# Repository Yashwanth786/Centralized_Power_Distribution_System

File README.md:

<div align="center">

# Centralized Power Distribution System

### IIT Hyderabad — Electrical Engineering Laboratory

*An IoT-based smart power management system for EE lab workbenches. Students request table power through a web portal by entering their roll number; lab staff monitor and control all 10 tables in real time from a central dashboard — powered by ESP32-C3 microcontrollers, Firebase Realtime Database, and automatic 18650 Li-Ion battery backup.*

<br>

<br>

</div>

---

## Table of Contents

1. [Introduction & Overview](#1-introduction--overview)
2. [Features](#2-features)
3. [System Architecture](#3-system-architecture)
4. [How It Works](#4-how-it-works)
5. [Hardware Design](#5-hardware-design)
6. [Software Design & Frameworks](#6-software-design--frameworks)
7. [Repository Structure](#7-repository-structure)
8. [Setup & Workflow](#8-setup--workflow)
9. [How to Run](#9-how-to-run)
10. [Portal Walkthrough — Screenshots](#10-portal-walkthrough--screenshots)
11. [Demo Video](#11-demo-video)
12. [Applications](#12-applications)
13. [Challenges Faced](#13-challenges-faced)
14. [Future Improvements](#14-future-improvements)
15. [Team](#15-team)

---

## 1. Introduction & Overview

University EE labs share 10 workbenches between many student groups. Today, a lab staff member must physically walk to each table to switch power on or off, and there is no record of who used which table, when, or for how long. Power is sometimes left ON after students leave, equipment runs unattended, and there is no centralized emergency cut-off.

The **Centralized Power Distribution System (CPDS)** eliminates this entirely. A custom PCB at each table drives three relay-controlled socket outlets under the control of a cloud-connected **Seeed Studio XIAO ESP32-C3**. A **React + Firebase** web portal provides two portals in one URL — a **Student Portal** where students type their roll number and choose an available table, and a **Staff Dashboard** where one instructor sees all 10 tables live and can cut any session in one click.

Communication flows through **Firebase Realtime Database** — the portal writes `isOn: true` to a table's path, the ESP32 there reads it within 2 seconds and closes the relays, and the sockets go live. All events are logged with timestamps. A built-in 18650 Li-Ion battery automatically takes over if mains power is lost, and a physical emergency button on each table cuts power instantly without needing a network round-trip.

---

## 2. Features

| Feature | Description |
|---|---|
| **Manual Roll Number Entry** | Students type their roll number in the portal — no QR scan, no app install, works on any browser |
| **Live Table Availability** | Student portal dropdown shows only currently available (unoccupied) tables in real time |
| **3-Hour Session Timer** | Each table allocation runs for 3 hours; staff dashboard shows live countdown per table |
| **Staff Dashboard** | Live grid of all 10 tables: status badge, student roll, session start time, countdown, power source, and action button |
| **Firebase Real-Time Sync** | Portal ↔ ESP32 changes propagate in under 2 seconds via Firebase `onValue` listeners |
| **Mains / Battery Auto-Failover** | ADC on GPIO D0 monitors mains via voltage divider; AO3401A P-MOSFET switches to 18650 + MT3608 boost when mains drops |
| **Physical Emergency Button** | NO push button on each table — immediately cuts all 3 relays and writes to Firebase without waiting for a network response |
| **Bi-Color LED Indicator** | Green = mains present & running; Red = battery mode / error / boot |
| **10-Second Heartbeat** | Each ESP32 writes `lastSeen` every 10 s; dashboard shows 🔴 Offline if heartbeat stops |
| **Activity Log Panel** | Every session start, end, expiry, emergency, and power event is logged to Firebase with a human-readable timestamp |
| **All-Off Emergency Button** | Staff button with confirmation modal cuts power to all 10 tables simultaneously |
| **Session Auto-Expiry** | Dashboard `Countdown` component auto-calls `deallocateTable()` when a 3-hour session reaches zero |
| **Recent Allocations Table** | Student roll-entry page shows the last 5 active allocations live — helps students see if their table is already taken |

---

## 3. System Architecture

```
┌──────────────────────────────────────────────────────────────────────┐
│                          Firebase Cloud                              │
│                                                                      │
│   Realtime Database                    Firebase Hosting              │
│   ────────────────                     ────────────────              │
│   tables/T-XX/isOn          ◄──────    React Web Portal             │
│   tables/T-XX/studentRoll              ├── Student Portal            │
│   tables/T-XX/starttimeLabel  ──────►  │   Roll number entry         │
│   tables/T-XX/sessionEnd               │   Table selection           │
│   power/T-XX/source         ◄──────    │   Confirmation screen       │
│   power/T-XX/lastSeen                  └── Staff Dashboard           │
│   logs/{id}                                All 10 tables live        │
│   logCount                                 End Session / All Off     │
└──────────────────────┬───────────────────────────────────────────────┘
                       │  Wi-Fi  IEEE 802.11 b/g/n
         ┌─────────────┼──────────────┐
         │             │              │
   ┌─────▼──────┐ ┌────▼───────┐ ┌──▼──────────┐
   │  Table T-01│ │ Table T-02 │ │  Table T-10  │
   │ XIAO ESP32 │ │ XIAO ESP32 │ │  XIAO ESP32  │
   │ Custom PCB │ │ Custom PCB │ │  Custom PCB  │
   │ ULN2003APG │ │ ULN2003APG │ │  ULN2003APG  │
   │ 3× Relays  │ │ 3× Relays  │ │  3× Relays   │
   │ HLK-PM01   │ │ HLK-PM01   │ │  HLK-PM01    │
   │ 18650+MT36 │ │ 18650+MT36 │ │  18650+MT36  │
   │ Emerg Btn  │ │ Emerg Btn  │ │  Emerg Btn   │
   │ Bi-clr LED │ │ Bi-clr LED │ │  Bi-clr LED  │
   └────────────┘ └────────────┘ └──────────────┘
```

**Data flow summary:**
- Student submits roll number → `allocateTable(id, roll)` → Firebase `tables/T-XX/isOn = true`
- ESP32 polls Firebase every 2 s → reads `isOn = true` → `setRelays(true)` → sockets live
- ESP32 writes `power/T-XX/lastSeen` every 10 s → dashboard flags Offline if missed
- Staff clicks End Session → `deallocateTable(id)` → Firebase `isOn = false` → ESP32 reads → relays open

---

## 4. How It Works

### Student Flow

```
Student opens web portal on any browser
              │
              ▼
Home Page  →  clicks "Student Portal" card
              │
              ▼
Roll Number Entry page (StudentScanPage):
  - Text input: type roll number e.g. "EE22BTECH11001"  →  press Next / Enter
  - Recent Allocations table shows last 5 active sessions live from Firebase
              │
              ▼
Table Selection page (StudentSelectPage):
  - Dropdown populated in real time with ONLY unoccupied tables
  - Occupied tables are excluded automatically
  - If all tables are full → yellow warning banner appears
  - Student selects table  →  "Allocate Table"
              │
              ▼
allocateTable("T-03", "EE22BTECH11001") writes to Firebase:
     tables/T-03/isOn            = true
     tables/T-03/studentRoll     = "EE22BTECH11001"
     tables/T-03/starttimeLabel  = "07/05/2026, 03:45:12 pm"
     tables/T-03/sessionEnd      = <epoch ms + 3 hours>
     tables/T-03/sessionEndLabel = "07/05/2026, 06:45:12 pm"
     logs/{n}                    = { type: "session_start", ... }
              │
              ▼
Confirmation page (StudentConfirmPage):
  - Shows roll number + table number (large green)
  - "Power is ON — please go to the table"
  - Session duration: 3 Hours
  - Auto-redirects to home in 5 seconds
              │
              ▼
ESP32 at T-03: polls Firebase (every 2 s)
  reads isOn = true  →  setRelays(true)
  D4, D3, D2 HIGH  →  ULN2003 drives coils  →  relay contacts close  →  sockets LIVE
  Green LED ON
```

### Staff Flow

```
Staff opens portal  →  "Technical Staff Portal"  →  Password entry
              │
              ▼
StaffLoginPage:
  - Password compared against hardcoded STAFF_PASSWORD
  - Correct  →  sessionStorage.setItem("staffAuth","true")  →  navigate to dashboard
  - Wrong    →  inline error message, password cleared
              │
              ▼
StaffDashboardPage (auth guard: redirects if staffAuth not set):
  - Three Firebase listeners started on mount:
      subscribeToTables  →  setTables state
      subscribeToPower   →  setPower  state
      subscribeToLogs    →  setLogs   state
  - Cleanup: all three unsubscribed on unmount
              │
              ▼
Dashboard header shows live stats chips: "3 Occupied  |  6 Available  |  1 Offline"

Dashboard table row per T-01…T-10:
  [Table ID] [Status badge] [Student Roll] [Start Time] [Countdown] [Power badge] [Action]
              │
              ▼
Staff clicks "⛔ End Session" on T-03:
  →  deallocateTable("T-03", "staff_ended")
  →  Firebase: isOn=false, lastUsed=<now>
  →  log: { type:"session_end", message:"Table T-03 session ended — reason: staff_ended" }
  →  ESP32 reads isOn=false on next 2s poll  →  setRelays(false)  →  sockets dead
              │
              ▼
Staff clicks "⛔ ALL OFF"  →  confirmation modal appears
  →  "Yes, ALL OFF"  →  allTablesOff()
  →  Promise.all: all 10 tables set isOn=false simultaneously
  →  log: { type:"staff", message:"ALL TABLES turned OFF by staff" }
```

### Emergency Button (Hardware)

```
Student presses NO push button on table edge (GPIO D1, INPUT_PULLUP)
              │
              ▼
ESP32 loop: digitalRead(PIN_EMERG_BTN) = LOW
50 ms debounce elapsed, btnWasPressed was false
              │
              ▼
emergTripped = true
setRelays(false) IMMEDIATELY — no Firebase wait
D4, D3, D2 → LOW  →  relay contacts open  →  sockets DEAD
              │
              ▼
Firebase writes (best-effort):
  firebaseDeallocate("emergency_button")  →  tables/T-XX/isOn = false
  firebaseAddLog("Emergency button pressed — relays OFF", "emergency")
Red LED ON
              │
              ▼
Button released: btnWasPressed=false, emergTripped=false (auto-reset latch)
Table ready for next student
```

### Mains Failure & Battery Failover

```
Mains power drops  →  HLK-PM01 output falls
              │
              ▼
ADC on GPIO D0 reads voltage divider:  analogRead(PIN_MAINS_ADC) < 500
mains (bool) becomes false, lastMailsState was true → change detected
              │
              ▼
updateLED(false): Green OFF, Red ON
firebaseSetPower("battery"):
  power/T-XX/source   = "battery"
  power/T-XX/lastSeen = <readable time>
              │
              ▼
If relays were ON when mains dropped:
  setRelays(false)
  firebaseDeallocate("mains_lost")
  firebaseAddLog("Mains power lost — relays turned OFF", "power")
              │
              ▼
AO3401A P-MOSFET hardware path (automatic, no firmware needed):
  HLK-PM01 rail drops  →  MOSFET gate control switches
  18650 Li-Ion  →  MT3608 boost converter  →  5V rail maintained
  ESP32 and relays stay powered
              │
              ▼
Mains restored: ADC rises above 500, mains=true again
updateLED(true): Green ON, Red OFF
firebaseSetPower("mains")
firebaseAddLog("Mains power restored", "power")
```

---

## 5. Hardware Design

### PCB Overview

Custom 2-layer PCB designed in **KiCad 9**. One board per lab table — 10 boards total.

| Parameter | Value |
|---|---|
| Design Tool | KiCad 9.x |
| Layers | 2 — F.Cu (signal + power) / B.Cu (High Voltage AC Power) |
| Min trace width | 0.3 mm signal / 1.5 mm mains |
| Mains isolation | 3 mm creepage gap + PCB slot (Edge.Cuts) |
| Surface finish | HASL |
| Board thickness | 1.6 mm |
| Copper weight | 1 oz (35 µm) |

### Schematic

### PCB Layout

### Pin Map — XIAO ESP32-C3

| Label | GPIO | Direction | Function |
|---|---|---|---|
| D0 | 2 | INPUT (ADC 12-bit) | Voltage divider output — mains sense, threshold 500 |
| D1 | 3 | INPUT (INPUT_PULLUP) | Emergency button — NO contact, active LOW |
| D2 | 4 | OUTPUT | ULN2003 I3 → Relay 3 — HIGH = relay energised = socket ON |
| D3 | 5 | OUTPUT | ULN2003 I2 → Relay 2 |
| D4 | 6 | OUTPUT | ULN2003 I1 → Relay 1 |
| D5 | 7 | OUTPUT | Green LED — HIGH = mains present, no error |
| D10 | 10 | OUTPUT | Red LED — HIGH = battery mode / error / boot |

### Power Architecture

```
230V AC Mains
     │
 [Varistor MOV]   ← surge protection
     │
 [HLK-PM01]       ← isolated SMPS, 230VAC → 5V DC
     │
     ├──────────── 5V Rail ─────────────────────────────────────┐
     │                                                          │
     │         [TP4056 charger] ←─── charges 18650 from 5V     │
     │                │                                         │
     │           [18650 Li-Ion]                                 │
     │                │                                         │
     │           [MT3608 Boost] → 5V                            │
     │                │                                      [AO3401A P-MOSFET]
     │                └─────────────────────────────────────────┘
     │                                                          │
     └──────────────────────────── 5V Supply Rail ─────────────┘
                                         │
                              [ESP32-C3 + ULN2003 + 3× Relays]
```

- **Normal:** HLK-PM01 supplies the 5V rail; AO3401A gate held high → MOSFET OFF → battery path blocked
- **Mains failure:** HLK-PM01 drops; AO3401A switches → MT3608 boosts 18650 → 5V rail sustained
- **Charging:** TP4056 charges 18650 from the 5V mains rail while mains is present
- **Protection:** SS34 Schottky diodes on all relay flyback paths; Varistor on AC input for surge events

### Bill of Materials (BOM)

| # | Component | Description | MPN | Price (Rs.) | Qty |
|---|---|---|---|---|---|
| 1 | Seeed Studio XIAO ESP32-C3 | Wi-Fi microcontroller, USB-C, castellated | Generic | 600 | 1 |
| 2 | 5V 1-Channel Relay Module | SRD-05VDC-SL-C coil, 10A contacts | SRD-05VDC-SL-C | 33 | 3 |
| 3 | ULN2003APG (Toshiba) | 50V / 500mA 7-ch Darlington array — relay driver | ULN2003APG | 19 | 1 |
| 4 | Momentary Push Switch | NO contact, active-low emergency button | TSD001B07018A | 20 | 1 |
| 5 | Hi-Link HLK-PM01 | 230VAC → 5V / 3W isolated SMPS | HLK-PM01 | 200 | 1 |
| 6 | 18650 Li-Ion Battery | 3.7V, 2500mAh backup cell | INR18650-25P | 81 | 1 |
| 7 | 18650 Battery Holder | SMD/SMT single cell | 1042P | 33 | 1 |
| 8 | TP4056 Charging Module | Adjustable 1A Li-Ion charger | TP4056 | 14 | 1 |
| 9 | MT3608 Boost Converter | 2A max DC-DC step-up module | MT3608| 36 | 1 |
| 10 | Bi-Color LED | 5mm Red/Green dual indicator | XL-A524SURSYGW | 3 | 1 |
| 11 | 6-Pin DPDT Self-Lock Switch | Latching power switch | — | 6 | 1 |
| 12 | AO3401A MOSFET | P-channel SOT-23, mains/battery path switch | AO3401A | 4 | 1 |
| 13 | 3-Pin Screw Terminal | 3.5mm pitch — mains & load connections | XY302V-3.5-3P | 12 | 4 |
| 14 | SS34 Schottky Diode | 3A / 40V — relay flyback + path blocking | — | 7 | 4 |
| 15 | 22µH Inductor SMD | MT3608 boost converter inductor | ASPI-0630LR-220M-T15 | 70 | 1 |
| 16 | Varistor D15.5mm P7.5mm | MOV surge protection on AC input | 561KD10J | 14 | 1 |
| 17 | PCB | Total PCB manufacturing cost  | — | 2936 | 1 |

Total cost  = Rs. 4211 /-  per  Table.

### Component Footprints

| Component | KiCad Footprint | Library |
|---|---|---|
| XIAO ESP32-C3 | `SeeedStudio_XIAO_ESP32C3` | Custom (castellated pads) |
| Relay Module | `Relay_THT:HF41F` | Standard |
| ULN2003APG | `Package_DIP:DIP-16_W7.62mm` | Standard |
| Momentary Push Switch | `Button_Switch_THT:SW_PUSH_6mm` | Standard |
| HLK-PM01 | `Converter_ACDC:HLK-PM01` | Standard |
| 18650 Battery Holder | `BatteryHolder_THT:BatteryHolder_Keystone_1042P` | Standard |
| TP4056 Module | `Module_TP4056` | Custom |
| MT3608 Boost Module | `Module_MT3608` | Custom |
| AO3401A MOSFET | `mosfet.pretty:SOT23-3` | Custom — included in `kicad/mosfet.pretty/` |
| Bi-Color LED | `LED_THT:LED_D5.0mm_2pin` | Standard |
| 3-Pin Screw Terminal | `TerminalBlock_Phoenix:MKDS_3-3.5` | Standard |
| 100µF Cap DIP | `Capacitor_THT:CP_Radial_D8.0mm_P3.50mm` | Standard |
| 22µF Cap DIP | `Capacitor_THT:CP_Radial_D6.3mm_P2.50mm` | Standard |
| SS34 Schottky Diode | `Diode_THT:D_DO-201AD` | Standard |
| 22µH Inductor SMD | `Inductor_SMD:L_Bourns_SRR1260` | Standard |
| All THT Resistors | `Resistor_THT:R_Axial_DIN0207_L6.3mm_D2.5mm_P7.62mm` | Standard |
| Varistor | `Varistor_THT:RV_D15.5mm_P7.5mm` | Standard |

> **Note:** The `mosfet.pretty/` folder is included in `kicad/` as a relative-path library. The project will open without missing footprint errors on any machine as long as the folder structure is kept intact.

---

## 6. Software Design & Frameworks

### Tech Stack

| Layer | Technology | Details |
|---|---|---|
| Frontend | React 18.2 | `create-react-app` scaffold |
| Routing | React Router DOM v6.21 | `BrowserRouter` + `Routes` + `Route` |
| Database | Firebase Realtime Database v10.7 | Real-time `onValue` listeners + `set` / `update` writes |
| Auth | Session-based (hardcoded password) | `sessionStorage.setItem("staffAuth","true")` |
| Hosting | Firebase Hosting | Deployed via `firebase deploy` |
| Firmware | Arduino / C++ on ESP32-C3 | `Firebase_ESP_Client` by Mobizt, `ArduinoJson` by Blanchon |

### Page Map

| Route | Component | What it does |
|---|---|---|
| `/` | `HomePage` | Landing — two hover cards: Technical Staff Portal & Student Portal |
| `/student/scan` | `StudentScanPage` | Roll number text input + Enter key support + recent allocations live table |
| `/student/select` | `StudentSelectPage` | Live dropdown of available tables + "Allocate Table" button + loading state |
| `/student/confirm` | `StudentConfirmPage` | Success card — roll, table (large green), "power is ON", 5-second countdown redirect |
| `/staff/login` | `StaffLoginPage` | Password input with show/hide toggle — stores auth in sessionStorage |
| `/staff/dashboard` | `StaffDashboardPage` | Full dashboard — 3 Firebase listeners, 10-table grid, logs panel, ALL OFF modal |

### Firebase Database Schema

```json
{
  "tables": {
    "T-01": {
      "isOn": true,
      "studentRoll": "EE22BTECH11001",
      "starttimeLabel": "07/05/2026, 03:45:12 pm",
      "sessionEnd": 1715079912000,
      "sessionEndLabel": "07/05/2026, 06:45:12 pm"
    }
  },
  "power": {
    "T-01": {
      "source": "mains",
      "lastSeen": "07/05/2026, 03:50:00 pm"
    }
  },
  "logs": {
    "1": {
      "message": "Table T-01 allocated to student EE22BTECH11001",
      "tableId": "T-01",
      "type": "session_start",
      "timestamp": "07/05/2026, 03:45:12 pm"
    }
  },
  "logCount": 1
}
```

### Key Functions — `database.js`

| Function | Description |
|---|---|
| `subscribeToTables(cb)` | `onValue` on `tables/` — returns Firebase unsubscribe fn; called in useEffect cleanup |
| `subscribeToPower(cb)` | `onValue` on `power/` — same pattern |
| `subscribeToLogs(cb, limit)` | `onValue` on `logs/` with `orderByKey + limitToLast(100)`, sorted newest-first |
| `allocateTable(id, roll)` | Writes `isOn=true`, roll, start time label, sessionEnd epoch + label; adds `session_start` log |
| `deallocateTable(id, reason)` | Writes `isOn=false`, `lastUsed`; adds `session_end` or `expire` log based on reason |
| `allTablesOff()` | `Promise.all` over all 10 table deallocations; adds single `staff` log |
| `clearLogs()` | Sets `logs` and `logCount` to null/0 |
| `clearAllData()` | Called on `App.js` mount — resets all tables to `isOn:false` and power to `offline` |
| `addLog({message, tableId, type})` | Reads `logCount`, increments, writes to `logs/{n}` with human timestamp |
| `toReadable(ms)` | Formats epoch ms → `"DD/MM/YYYY, HH:MM:SS am/pm"` (matches ESP32 output) |

### ESP32 Firmware — Timing Constants

| `#define` | Value | Purpose |
|---|---|---|
| `MAINS_THRESHOLD` | 500 (ADC counts) | 12-bit ADC reading below this = mains lost |
| `DEBOUNCE_MS` | 50 ms | Emergency button software debounce window |
| `FIREBASE_POLL_MS` | 2000 ms | Interval between Firebase `getBool` reads for `isOn` |
| `HEARTBEAT_INTERVAL_MS` | 10000 ms | Interval between `lastSeen` + power source writes |

### App.js — Startup Behaviour

On every portal load, `App.js` calls `clearAllData()` in a `useEffect`. This resets all 10 tables to `isOn: false` and all power entries to `source: "offline"` — ensuring a clean slate each time staff open the portal.

---

## 7. Repository Structure

```
centralized-power-distribution/
│
├── README.md                              ← This file
├── PCB.pdf                                ← Hardware reference (schematic, BOM, footprints, gerbers)
├── .gitattributes
│
├── kicad/                                 ← All KiCad design files
│   ├── lab.kicad_pro                      ← Open this in KiCad 7 to load the full project
│   ├── lab.kicad_sch                      ← Complete schematic
│   ├── lab.kicad_pcb                      ← PCB layout with copper pours and component placements
│   ├── lab.kicad_prl                      ← Project-level layer/render preferences
│   ├── New_Library.kicad_sym              ← Custom schematic symbols library
│   ├── mosfet.kicad_sym                   ← AO3401A schematic symbol
│   ├── mosfet.pretty/
│   │   └── SOT23-3.kicad_mod              ← Custom AO3401A PCB footprint (SOT-23-3, 0.95mm pitch)
│   ├── sym-lib-table                      ← Symbol library path references
│   ├── fp-lib-table                       ← Footprint library path references
│   └── lab_output/                        ← Gerber files — ZIP this folder and send to manufacturer
│       ├── lab-F_Cu.gbr                   ← Front copper traces
│       ├── lab-B_Cu.gbr                   ← Back copper ground plane
│       ├── lab-F_Mask.gbr                 ← Front solder mask
│       ├── lab-B_Mask.gbr                 ← Back solder mask
│       ├── lab-F_Silkscreen.gbr           ← Front silkscreen labels
│       ├── lab-B_Silkscreen.gbr           ← Back silkscreen
│       ├── lab-F_Paste.gbr                ← Front solder paste
│       ├── lab-B_Paste.gbr                ← Back solder paste
│       ├── lab-Edge_Cuts.gbr              ← Board outline + isolation PCB slot
│       ├── lab-PTH.drl                    ← Plated through-hole drill file
│       ├── lab-NPTH.drl                   ← Non-plated through-hole drill file
│       └── lab-job.gbrjob                 ← Gerber job metadata file
│
├── esp32-code/
│   └── lab_controller_v3.ino          ← Full ESP32-C3 Arduino firmware (v3.0)
│
├── web-portal/
│   ├── package.json                       ← React 18 + React Router v6 + Firebase v10 dependencies
|   ├── package-lock.json                  ← Exact locked dependency versions for reproducible npm installs
|   ├── README.md                          ← Setup flow for website and esp32
|   ├── public/
|   |   ├── index.html                     ← Basic frame for portal 
|   ├── esp32_firmware/
│   |   ├── lab_controller_v3.ino          ← Full ESP32-C3 Arduino firmware (v3.0) (same as above used esp32-code)
│   └── src/
│       ├── App.js                         ← BrowserRouter root — 6 routes + clearAllData on mount
│       ├── index.js                       ← React DOM entry point
│       ├── index.css                      ← CSS variables (--orange, --bg, --border, etc.) + globals
│       ├── iit-logo.png                   ← IITH logo used in HomePage and IITBrand panel
│       ├── firebase/
│       │   ├── config.js                  ← Firebase app init — reads from .env variables
│       │   └── database.js                ← All Firebase helper functions and subscriptions
│       ├── pages/
│       │   ├── HomePage.jsx               ← Landing page — two portal cards
│       │   ├── StudentScanPage.jsx        ← Roll number input + recent allocations table
│       │   ├── StudentSelectPage.jsx      ← Available table dropdown + Allocate button
│       │   ├── StudentConfirmPage.jsx     ← Success card + 5s countdown redirect
│       │   ├── StaffLoginPage.jsx         ← Password login + sessionStorage auth
│       │   └── StaffDashboardPage.jsx     ← Full dashboard — grid, logs, ALL OFF modal
│       └── components/
│           └── IITBrand.jsx               ← Left-panel branding strip with logo + lab name
│
└── media/
    ├── demo_video.mp4                     ← Full system demonstration video
    ├── screenshots/
    │   ├── 01_home_page.png               ← Home page — two portal cards
    │   ├── 02_student_roll_entry.png      ← Roll number text input + recent allocations
    │   ├── 03_student_table_select.png    ← Available tables dropdown
    │   ├── 04_student_confirmation.png    ← Confirmation card with table number
    │   ├── 05_staff_login.png             ← Staff password login screen
    │   └── 06_staff_dashboard.png         ← Full dashboard — all 10 tables live
    └── hardware/
        ├── system_overview.jpg            ← Wide shot of full table setup
        ├── schematic.png                  ← KiCad schematic export
        ├── pcb.png                        ← KiCad 3D render
        └── pcb_3d_top.png                 ← KiCad 3D viewer top render (raytracing)
```

---

## 8. Setup & Workflow

### Prerequisites

- Node.js ≥ 16 and npm
- Arduino IDE 2.x
- KiCad 9.x (for PCB files)
- A Firebase project with Realtime Database enabled

### Step 1 — Firebase Project

1. Go to [console.firebase.google.com](https://console.firebase.google.com) → **Create project**
2. Enable **Realtime Database** — choose Asia Southeast 1 for lowest latency from India
3. Set temporary development rules:
   ```json
   { "rules": { ".read": true, ".write": true } }
   ```
4. Copy your **Web API Key** from Project Settings → General
5. Copy your **Database URL** from the Realtime Database panel
6. Create a **Legacy Database Secret** from Project Settings → Service Accounts → Database Secrets — this is needed by the ESP32

### Step 2 — Web Portal

```bash
cd web-portal/
npm install
```

#### File 1 — Firebase credentials
Open ``` web-portal/src/firebase/config.js ``` and replace the values directly:

```js
const firebaseConfig = {
  apiKey:            "YOUR_WEB_API_KEY",
  authDomain:        "YOUR_PROJECT_ID.firebaseapp.com",
  databaseURL:       "https://YOUR_PROJECT_ID-default-rtdb.asia-southeast1.firebasedatabase.app",
  projectId:         "YOUR_PROJECT_ID",
  storageBucket:     "YOUR_PROJECT_ID.appspot.com",
  messagingSenderId: "YOUR_SENDER_ID",
  appId:             "YOUR_APP_ID"
};
```

#### File 2 — Staff password
Open ``` web-portal/src/pages/StaffLoginPage.jsx ``` and find line near the top:
```js
const STAFF_PASSWORD = "your_chosen_password";
```

### Step 3 — ESP32 Firmware

**Install Arduino libraries** (Tools → Manage Libraries):
- `Firebase ESP Client` by Mobizt
- `ArduinoJson` by Benoit Blanchon

**Add XIAO board package** — File → Preferences → Additional Boards Manager URLs:
```
https://raw.githubusercontent.com/espressif/arduino-esp32/gh-pages/package_esp32_index.json
```
Then install `esp32 by Espressif Systems` in Boards Manager.

**Edit the 5 marked lines** at the top of `lab_controller_v3.ino`:
```cpp
#define WIFI_SSID         "YOUR_WIFI_SSID"        // your Wi-Fi network name
#define WIFI_PASSWORD     "YOUR_WIFI_PASSWORD"     // your Wi-Fi password
#define TABLE_ID          "T-01"                   // change per board: T-01 … T-10
#define FIREBASE_API_KEY  "YOUR_WEB_API_KEY"       // from Firebase Project Settings → General
#define DATABASE_URL      "YOUR_DATABASE_URL"      // from Firebase Realtime Database panel
```

Also update the legacy token:
```cpp
config.signer.tokens.legacy_token = "YOUR_DATABASE_SECRET"; // from Project Settings → Service Accounts → Database Secrets
```

**Arduino IDE board settings:**

| Setting | Value |
|---|---|
| Board | XIAO_ESP32C3 |
| Upload Speed | 921600 |
| USB CDC On Boot | Enabled |

Flash each of the 10 boards with a unique `TABLE_ID` (`T-01` through `T-10`). After flashing, open Serial Monitor at **115200 baud** — first lines should be:
```
=== IIT-H EE Lab ESP32 v3.0 ===
Table: T-01
[WiFi] Connecting to YOUR_SSID
[Firebase] Connected OK
[Boot] Ready.
```

---

## 9. How to Run

### Web Portal — Development

```bash
cd web-portal/
npm start
# Opens at http://localhost:3000
```

### Web Portal — Production (Firebase Hosting)

```bash
npm run build
npm install -g firebase-tools
firebase login
firebase init hosting
# → Public dir: build
# → Configure as SPA: Yes
# → Overwrite build/index.html: No
firebase deploy
# Live at https://your-project.web.app
```

### ESP32 Boards

1. Connect XIAO ESP32-C3 via USB-C
2. Set the correct `TABLE_ID` for this board
3. Select the correct port in Arduino IDE
4. Click Upload (Ctrl+U)
5. Verify serial output shows correct TABLE_ID
6. Repeat for all 10 boards (T-01 → T-10)

Once all boards are powered and connected to Wi-Fi, the staff dashboard will show ⚡ Mains for each online table within 10 seconds (first heartbeat).

---

## 10. Portal Walkthrough — Screenshots

### Home Page

The landing page displays the IIT Hyderabad logo, university name, and lab title. Two clickable cards navigate to the Staff and Student portals. Cards lift and border turns orange on hover.

---

### Student — Roll Number Entry

Students type their roll number (e.g. `EE22BTECH11001`) and press **Next** or hit Enter. A "Recent Allocations" table below the input shows the last 5 active sessions — roll number, table, and date — pulled live from Firebase.

---

### Student — Table Selection

A dropdown lists only currently unoccupied tables in real time. The page shows how many tables are available. If all tables are occupied, a yellow warning banner appears instead of the dropdown. Student selects a table and clicks **Allocate Table**.

---

### Student — Confirmation

A green-bordered card confirms the allocation: roll number, allotted table number displayed large in green, "please go to the table, the power is ON", and session duration (3 hours). The page automatically redirects back to home after 5 seconds.

---

### Staff — Login

A centered card with a lock icon and a password field. The 👁️ button toggles password visibility. Correct password stores `staffAuth` in `sessionStorage` and navigates to the dashboard. Wrong password shows an inline red error.

---

### Staff — Dashboard

The full control centre. A sticky orange header shows "Technical Staff Portal", live status chips (Occupied / Available / Offline counts), a **Show Logs** toggle, and the red **⛔ ALL OFF** emergency button.

The main table has one row per lab table (T-01 to T-10), each showing:
- **Table ID** — bold identifier
- **Status badge** — 🟢 Available / 🟠 Occupied (pulsing dot) / ⚫ Off
- **Student Roll** — monospace, shown only when occupied
- **Start Time** — human-readable session start timestamp
- **Time Remaining** — live `HH:MM:SS` countdown (turns red in last 10 minutes)
- **Power Source** — ⚡ Mains / 🔋 Battery / 🔴 Offline
- **⛔ End Session** — red button visible only for occupied tables

The **Activity Logs** panel (toggled from header) shows all events with type-coded badges: SESSION START / SESSION END / EXPIRE / EMERGENCY / POWER / STAFF. A "Clear Logs" button resets the log in Firebase.

---

## 11. Demo Video

Watch the demo video here: [Demo Video](https://drive.google.com/file/d/1mhNnTaNkejmopCFQ-6PinY2lMFn2YFTQ/view?usp=sharing))

**What the demo shows:**
1. Student enters roll number → selects table → confirmation screen → sockets go live
2. Staff dashboard updates in real time — table flips to Occupied with live countdown
3. Staff ends session from dashboard → relays cut → table returns to Available
4. Emergency button press on table → immediate relay cutoff → dashboard updates to Off
5. Mains disconnected → battery failover → 🔋 Battery badge appears on dashboard

---

## 12. Applications

| Domain | Use Case |
|---|---|
| University EE Labs | Controlled, authenticated, logged power access for shared workbenches — primary use case |
| School Electronics Labs | Staff-supervised power control preventing unsupervised student equipment use |
| Makerspaces | Per-member metered power access with session logging and time limits |
| Industrial Test Stations | Remote power management for shared test benches in manufacturing or R&D environments |
| Exam / Assessment Centres | Timed, per-seat power allocation with automatic expiry for practical examinations |

---

## 13. Challenges Faced

| # | Challenge | Category | Resolution |
|---|---|---|---|
| 1 | ADC mains-sense gave noisy readings — false failover triggers every few seconds | Hardware | Added 100µF + 22µF capacitors across voltage divider output to GND; 5-consecutive-reading hysteresis in firmware |
| 2 | Relay chatter during mains → battery transition (~80 ms power sag caused ESP32 brownout) | Hardware | Added 100µF bulk capacitor directly on 5V rail near ESP32 VCC pin — bridges the switchover gap |
| 3 | AO3401A gate drive: ESP32 3.3V GPIO cannot fully turn OFF a 5V P-channel MOSFET | Hardware | Added NPN transistor level-shift stage; 120kΩ pull-up to 5V rail for proper gate-high state |
| 4 | KiCad standard library had no AO3401A SOT-23-3 footprint at correct 0.95mm pin pitch | Hardware | Created `mosfet.pretty` custom footprint library — included in the repo |
| 5 | Initial PCB layout violated IPC-2221 mains creepage distance between AC and DC traces | Hardware | Redesigned layout with 3mm gap + physical PCB slot in Edge.Cuts layer |
| 6 | Firebase streaming (persistent HTTPS) connection dropped frequently on lab Wi-Fi idle timeout | Firmware | Switched to 2-second polling with `Firebase.RTDB.getBool()` — stable, latency acceptable for power control |
| 7 | Emergency button mechanical bounce caused 3–5 spurious `LOW` reads per single press | Firmware | 50 ms software debounce + `btnWasPressed` latch; latch clears only on release (HIGH), not press |
| 8 | `onValue` listeners stacked on re-navigation — 3 → 6 → 9 active listeners after 3 visits to dashboard | Software | `useEffect` cleanup returns and calls all three Firebase unsubscribe functions on component unmount |
| 9 | Session countdown timer drifted 5–10 s per hour using `setInterval` decrement counter | Software | Changed to `Math.max(0, sessionEnd - Date.now())` per tick — always accurate, drift-free |

---

## 14. Future Improvements

- **OTA Firmware Updates** — Push new firmware to all 10 boards wirelessly via Firebase Functions; eliminates need to physically connect each ESP32
- **EEPROM-Based TABLE_ID Provisioning** — Store TABLE_ID in flash memory; configure once over Serial without recompiling the firmware
- **Energy Metering** — Add INA219 current sensor per table; log per-session energy consumption (Wh / kWh) to Firebase
- **Admin Analytics Dashboard** — Usage heat maps, per-table uptime percentages, peak hours graphs, battery health indicators
- **Email / SMS Alerts** — Notify staff automatically when a table goes offline, battery is low, or an emergency is triggered
- **RFID / ID Card Authentication** — Replace manual roll number typing with RFID card tap for faster, error-free student identification
- **Tighter Firebase Security Rules** — Rate-limit student allocations; validate roll number format server-side; restrict `isOn` writes to authenticated users only
- **Progressive Web App (PWA)** — Add service worker and manifest so students can install the portal to their phone home screen with offline fallback

---

## 15. Team

| Name | Role Number | Contribution |
|---|---|---|
| Chinthalapudi Yashwanth | EE22BTECH11016 | Hardware Design & PCB Layout (KiCad) |
| Abburi Naga Sai Ram | EE22BTECH11201 | ESP32 Firmware & Web Portal Development |

**Institution:** Indian Institute of Technology Hyderabad  
**Department:** Electrical Engineering  
**Course:** Electronic System Design Project Lab  
**Faculty Advisor:** Dr. Abhishek Kumar   
**Academic Year:** 2025–26

---

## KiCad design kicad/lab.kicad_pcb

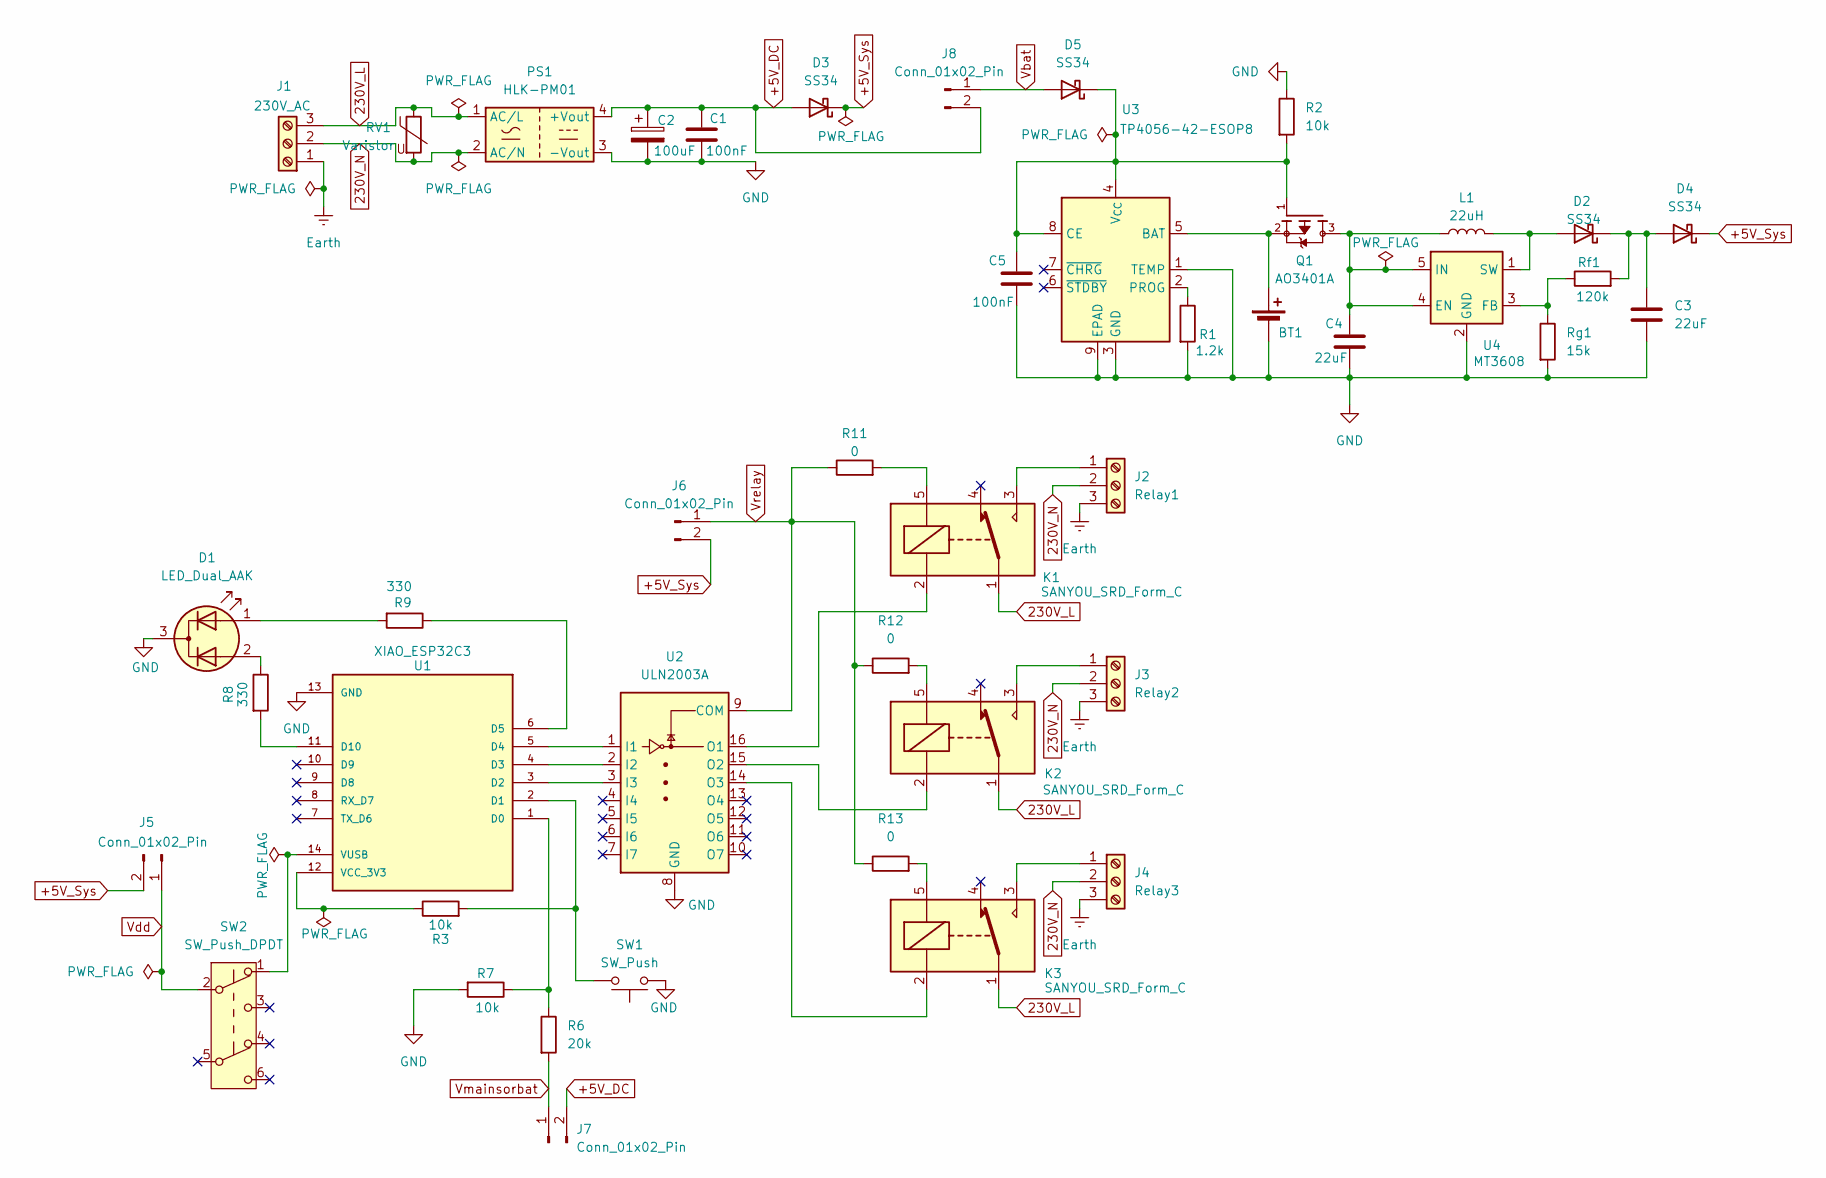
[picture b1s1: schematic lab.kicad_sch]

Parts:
BT1: 18650_Li_Ion; BatteryHolder_Keystone_1042_1x18650
C1, C5: 100nF; C_Disc_D5.0mm_W2.5mm_P5.00mm
C2: 100uF; CP_Radial_D8.0mm_P3.50mm
C3, C4: 22uF; C_Disc_D5.0mm_W2.5mm_P5.00mm
D1: LED_Dual_AAK; LED_D5.0mm-3
D2, D3, D4, D5: SS34; D_SMA
J1: 230V_AC; TerminalBlock_Phoenix_PT-1,5-3-3.5-H_1x03_P3.50mm_Horizontal
J2: Relay1; TerminalBlock_Phoenix_PT-1,5-3-3.5-H_1x03_P3.50mm_Horizontal
J3: Relay2; TerminalBlock_Phoenix_PT-1,5-3-3.5-H_1x03_P3.50mm_Horizontal
J4: Relay3; TerminalBlock_Phoenix_PT-1,5-3-3.5-H_1x03_P3.50mm_Horizontal
J5, J6, J7, J8: Conn_01x02_Pin; PinHeader_1x02_P2.54mm_Vertical
K1, K2, K3: SANYOU_SRD_Form_C; Relay_SPDT_SANYOU_SRD_Series_Form_C
L1: 22uH; L_Abracon_ASPI-0630LR
PS1: HLK-PM01; Converter_ACDC_Hi-Link_HLK-PMxx
Q1: AO3401A; SOT23-3
R1: 1.2k; R_Axial_DIN0204_L3.6mm_D1.6mm_P5.08mm_Vertical
R2, R3, R7: 10k; R_Axial_DIN0204_L3.6mm_D1.6mm_P5.08mm_Vertical
R6: 20k; R_Axial_DIN0204_L3.6mm_D1.6mm_P5.08mm_Vertical
R8, R9: 330; R_Axial_DIN0204_L3.6mm_D1.6mm_P5.08mm_Vertical
R11, R12, R13: 0; R_0805_2012Metric
RV1: Varistor; RV_Disc_D15.5mm_W3.9mm_P7.5mm
Rf1: 120k; R_Axial_DIN0204_L3.6mm_D1.6mm_P5.08mm_Vertical
Rg1: 15k; R_Axial_DIN0204_L3.6mm_D1.6mm_P5.08mm_Vertical
SW1: SW_Push; PinHeader_1x02_P2.54mm_Vertical
SW2: SW_Push_DPDT; SW_PUSH_E-Switch_FS5700DP_DPDT
U1: XIAO_ESP32C3; MODULE_XIAO_ESP32C3; PARTREV 23/05/2022
U2: ULN2003A; DIP-16_W7.62mm
U3: TP4056-42-ESOP8; SOIC-8-1EP_3.9x4.9mm_P1.27mm_EP2.41x3.3mm_ThermalVias
U4: MT3608; SOT-23-6

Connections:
230V_L: J1.3, K1.1, K2.1, K3.1, PS1.1 (AC/L), RV1.1
230V_N: J1.2, J2.2, J3.2, J4.2, PS1.2 (AC/N), RV1.2
+5V_DC: C1.1, C2.1, D3.2 (A), J7.2, J8.2, PS1.4 (+Vout)
+5V_Sys: D3.1 (K), D4.1 (K), J5.2, J6.2
Earth: J1.1, J2.3, J3.3, J4.3
GND: BT1.2 (-), C1.2, C2.2, C3.2, C4.2, C5.2, D1.3 (K), PS1.3 (-Vout), R1.2, R2.1, R7.2, Rg1.2, SW1.1, U1.13 (GND), U2.8 (GND), U3.1 (TEMP), U3.3 (GND), U3.9 (EPAD), U4.2 (GND)
unnamed: BT1.1 (+), Q1.2, U3.5 (BAT)
unnamed: D1.1 (A1), R9.2
unnamed: D1.2 (A2), R8.1
unnamed: D2.2 (A), L1.2, U4.1 (SW)
unnamed: C3.1, D2.1 (K), D4.2 (A), Rf1.2
unnamed: C5.1, D5.1 (K), Q1.1, R2.2, U3.4 (V_{CC}), U3.8 (CE)
unnamed: J2.1, K1.3
unnamed: J3.1, K2.3
unnamed: J4.1, K3.3
unnamed: K1.5, R11.2
unnamed: K2.5, R12.2
unnamed: K3.5, R13.2
unnamed: R6.1, R7.1, U1.1 (D0)
unnamed: R3.2, SW1.2, U1.2 (D1)
unnamed: U1.3 (D2), U2.3 (I3)
unnamed: U1.4 (D3), U2.2 (I2)
unnamed: U1.5 (D4), U2.1 (I1)
unnamed: R9.1, U1.6 (D5)
unnamed: R8.2, U1.11 (D10)
unnamed: R3.1, U1.12 (VCC_3V3)
unnamed: SW2.1 (A), U1.14 (VUSB)
unnamed: K1.2, U2.16 (O1)
unnamed: K2.2, U2.15 (O2)
unnamed: K3.2, U2.14 (O3)
unnamed: R1.1, U3.2 (PROG)
unnamed: C4.1, L1.1, Q1.3, U4.4 (EN), U4.5 (IN)
unnamed: Rf1.1, Rg1.1, U4.3 (FB)
Vbat: D5.2 (A), J8.1
Vdd: J5.1, SW2.2 (B)
Vmainsorbat: J7.1, R6.2
Vrelay: J6.1, R11.1, R12.1, R13.1, U2.9 (COM)

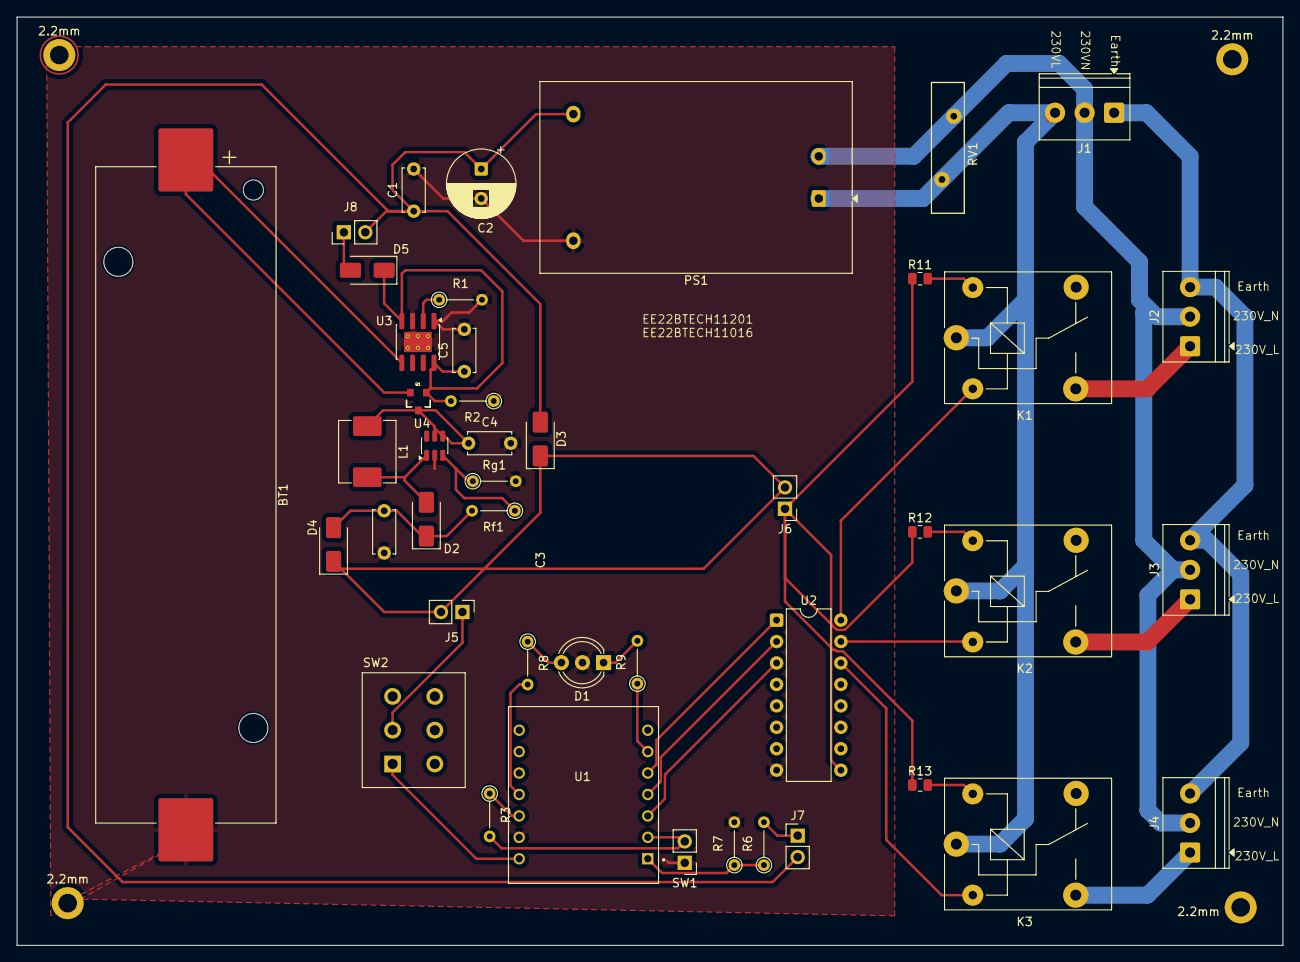
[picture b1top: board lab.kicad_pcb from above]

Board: 2 copper layers, 150.0 x 110.0 mm, 48 parts (0 on the bottom side), 37 nets.

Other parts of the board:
2.2mm, 2.2mm#2, 2.2mm#3, 2.2mm#4: MountingHole_2.2mm_M2_DIN965_Pad

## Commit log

2026-05-11 Initial commit with Git LFS
2026-05-11 pcb description
2026-05-11 kicad uploaded
2026-05-11 esp code uploaded
2026-05-11 website codes uploaded
2026-05-11 Create README.md for Centralized Power Distribution System
    Add detailed project documentation for the Centralized Power Distribution System, including system overview, features, architecture, and setup instructions.
